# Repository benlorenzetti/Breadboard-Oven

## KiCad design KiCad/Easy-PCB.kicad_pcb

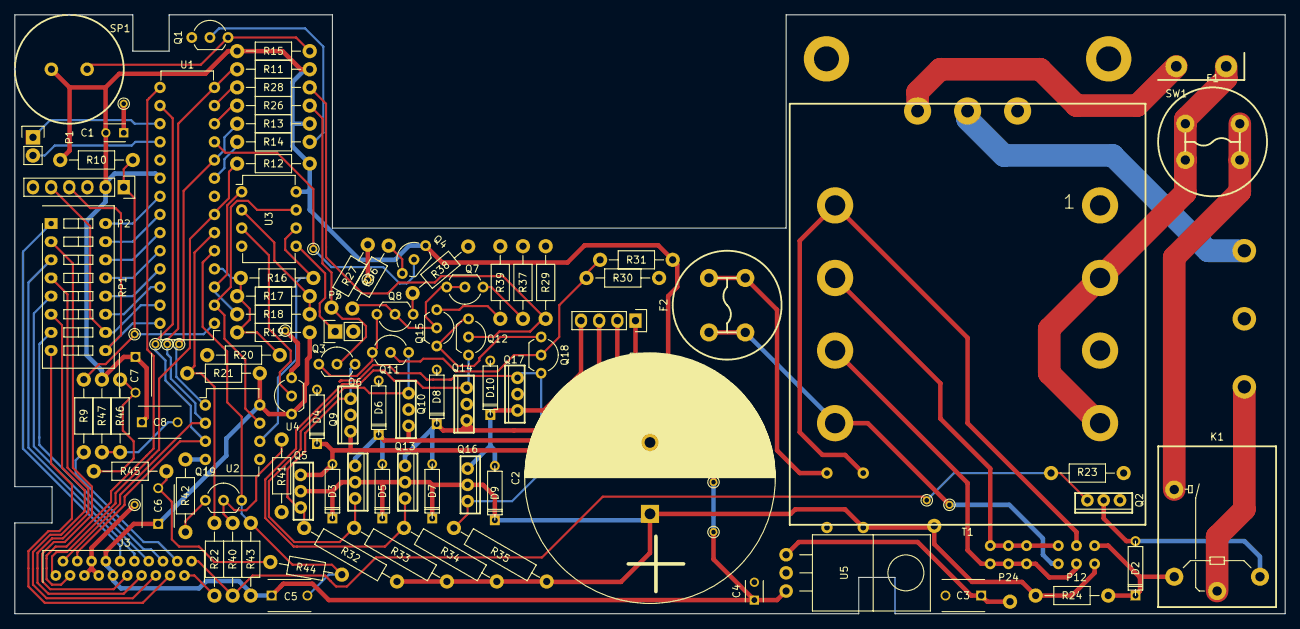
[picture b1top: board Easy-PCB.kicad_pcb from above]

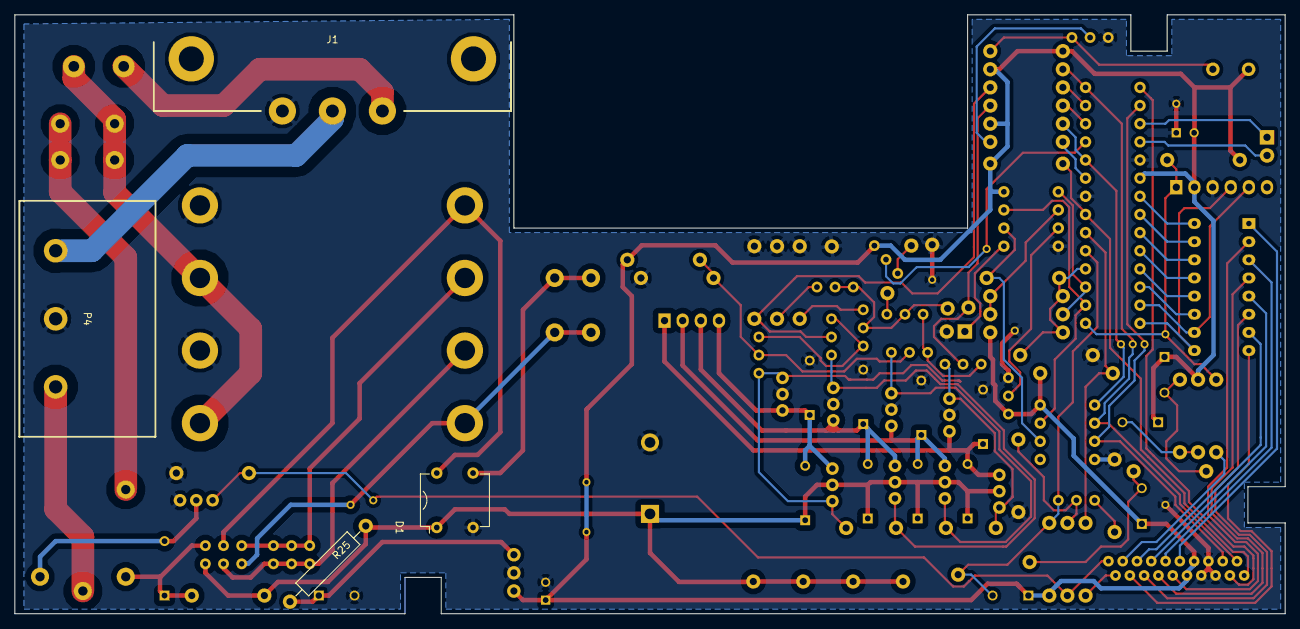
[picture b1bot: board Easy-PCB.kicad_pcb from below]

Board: 2 copper layers, 177.8 x 83.8 mm, 111 parts (4 on the bottom side), 81 nets.

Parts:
C1: 0.1u; C_Disc_D3_P2.5
C2: >16.6 mF; C_Radial_D35_L51_P10
C3: 0.33 uF; C_Disc_D6_P5
C4: 0.1 uF; C_Disc_D3_P2.5
C5, C6, C7, C8: CP1; C_Disc_D6_P5
D1: DF04M
D2: V*A(max) > 0.4 W; D3
D3, D4, D5, D6, D7, D8, D9, D10: D; D3
F1, F2: 83100000005; 83100000005_Fuse_Holder
J1: 703W-00/53; 703W-0053
J3: HLW20R-2C7LF
K1: G5LE-1A-E_DC12
P1, P5: 1x02; Socket_Strip_Straight_1x02
P2: 1x06; Socket_Strip_Straight_1x06
P3: 1x04; Socket_Strip_Straight_1x04
P4: 1x03 Terminal Block; 5-1437652-4
P6, P7, P8, P9, P10, P11, P13, P14, P15, P16, P17, P18, P19: via; PINTST
P12, P24: M20-9980346; Male_Header_2x03
P22: Screw Mounting; 10-32
Q1, Q3, Q4, Q7, Q8, Q11, Q12, Q15, Q18, Q19: 2N3904; TO-92
Q2, Q5, Q9, Q13, Q16: MJE340; MJE3x0
Q6, Q10, Q14, Q17: MJE350; MJE3x0
R9, R14, R15, R17, R20, R22: 1k; Resistor_Horizontal_RM10mm
R10, R11, R12, R13, R21: 10k; Resistor_Horizontal_RM10mm
R16: 100; Resistor_Horizontal_RM10mm
R18: 1.7k; Resistor_Horizontal_RM10mm
R19: 6.1k; Resistor_Horizontal_RM10mm
R23: 333; Resistor_Horizontal_RM10mm
R24: 330; Resistor_Horizontal_RM10mm
R25: 10 Ohm; >= 2W; Resistor_Horizontal_RM15mm
R26, R28: 140; Resistor_Horizontal_RM10mm
R27, R29: 115; Resistor_Horizontal_RM10mm
R30, R31: 64; Resistor_Horizontal_RM10mm
R32, R33, R34, R35: 165; Resistor_Horizontal_RM15mm
R36: 51; Resistor_Horizontal_RM10mm
R37, R38, R39: 10; Resistor_Horizontal_RM10mm
R40, R41, R42, R43, R44, R45, R46, R47: R; Resistor_Horizontal_RM10mm
RP1: 320; SW_DIP_x8_Slide
SP1: 2kHz Piezo; PS1420
SW1: R1966ABLKBLKFR
T1: VPP24-830
U1: PIC16F883; DIP-28
U2: MCP41050; DIP-8
U3: MCP617; DIP-8
U4: MCP9700A; TO-92
U5: LM7805; TO-220

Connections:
12Vrelay1: D2.1, K1.2, P12.6, R24.2
12Vrelay2: D2.2, K1.5, Q2.2
12or24VAC1: F2.1, F2.2, P8.1, P12.1, T1.12
12or24VAC2: D1.4, P12.4, T1.7
12or24VAC3: P12.3, P24.1, P24.3, P24.5, T1.10
12or24VAC4: P12.2, P24.2, P24.4, P24.6, T1.9
12or24VAC5: D1.3, F2.3, F2.4
/Analog Math/NichromeTemp: C5.2, Q19.3, R43.2, R44.2, U1.5
/Heat Relay/DoorC1: J3.19, R22.1
/Heat Relay/Heat: R21.2, R22.2, U1.6
/Heat Relay/HeatLive: K1.1, P4.1
/Motor Driver/wind1: R26.2, U1.12
/Motor Driver/wind1a: D3.2, D4.1, P3.1, Q5.1, Q6.1
/Motor Driver/wind1b: D5.2, D6.1, P3.2, Q9.1, Q10.1
/Motor Driver/wind2: R28.2, U1.13
/Motor Driver/wind2a: D7.2, D8.1, P3.3, Q13.1, Q14.1
/Motor Driver/wind2b: D9.2, D10.1, P3.4, Q16.1, Q17.1
/Power Circuit/MainsLive: F1.1, F1.2, SW1.2, T1.3, T1.6
/Temperature Feedback/K+: P5.1, U3.5
/Temperature Feedback/Tk: U1.2, U2.7, U3.7
/Temperature Feedback/Tref: R18.2, U1.3, U3.1
/Temperature Feedback/Vref-: R16.1, R17.1, R19.2, R20.1, U1.4
CS1: J3.1, R12.2, U1.7
CS2: P13.1, R13.2, U1.10, U2.1
DoorC2: J3.20, P9.1, Q2.3, R23.1, R40.2
Earth: J1.2, P4.3
GND: C1.1, C2.2, C3.2, C4.2, D1.2, D4.2, D6.2, D8.2, D10.2, J1.3, J3.5, J3.6, J3.7, P2.3, P4.2, P5.2, P14.1, P15.1, P17.1, P18.1, Q1.1, Q2.1, Q6.2, Q10.2, Q14.2, Q17.2, R20.2, R23.2, R27.2, R29.1, R31.2, R37.2, R38.2, R39.2, R41.2, R42.2, T1.1, T1.4, U1.8, U1.19, U2.4, U3.4, U4.3, U5.2
MISO: J3.3, U1.15
MOSI: J3.4, P10.1, U1.16, U2.3
Motor_On: P16.1, Q4.2, U1.11
unnamed: C6.2, R44.1, R45.2
unnamed: C7.2, R45.1, R46.2
unnamed: C8.2, R46.1, R47.2
unnamed: J1.1, SW1.1
unnamed: J3.10, RP1.1
unnamed: J3.11, RP1.2
unnamed: J3.12, RP1.3
unnamed: J3.13, RP1.4
unnamed: J3.14, RP1.5
unnamed: J3.15, RP1.6
unnamed: J3.16, RP1.7
unnamed: J3.17, RP1.8
unnamed: J3.18, R9.2
unnamed: P2.4, RP1.9, U1.28
unnamed: P2.5, RP1.10, U1.27
unnamed: Q1.2, R14.1
unnamed: Q1.3, R15.2, SP1.2
unnamed: Q3.2, R26.1, R27.1
unnamed: Q3.3, Q5.3, Q6.3, R32.2
unnamed: Q4.1, R36.2
unnamed: Q7.1, R37.1
unnamed: Q8.1, R38.1
unnamed: Q9.3, Q10.3, Q11.3, R33.2
unnamed: Q3.1, Q8.3, Q11.1
unnamed: Q11.2, Q18.2, R30.2, R31.1
unnamed: Q12.1, Q15.3, Q18.1
unnamed: Q12.2, R28.1, R29.2
unnamed: Q12.3, Q13.3, Q14.3, R34.2
unnamed: Q15.1, R39.1
unnamed: Q7.2, Q7.3, Q8.2, Q15.2, R36.1
unnamed: Q16.3, Q17.3, Q18.3, R35.2
unnamed: Q19.1, R42.1
unnamed: Q19.2, R40.1, R41.1
unnamed: R14.2, U1.9
unnamed: R16.2, U2.6, U3.6
unnamed: R17.2, R18.1, U3.2
unnamed: RP1.11, U1.26
unnamed: RP1.12, U1.25
unnamed: RP1.13, U1.24
unnamed: RP1.14, U1.23
unnamed: RP1.15, U1.22
unnamed: RP1.16, U1.21
unnamed: U3.3, U4.2
RX: P1.2, U1.18
Reset: P2.1, P19.1, R9.1, R10.2, U1.1
SCK: J3.2, P11.1, R11.2, U1.14, U2.2
TX: P1.1, U1.17
VAA: F1.3, F1.4, K1.3
VCC: C2.1, D1.1, D3.1, D5.1, D7.1, D9.1, P12.5, Q5.2, Q9.2, Q13.2, Q16.2, R24.1, R25.2, R32.1, R33.1, R34.1, R35.1
VDD: C1.2, C4.1, C5.1, C6.1, C7.1, C8.1, J3.8, J3.9, P2.2, P6.1, P7.1, Q4.3, R10.1, R11.1, R12.1, R13.1, R15.1, R19.1, R21.1, R30.1, R43.1, R47.1, SP1.1, U1.20, U2.8, U3.8, U4.1, U5.3
VDDunreg: C3.1, R25.1, U5.1

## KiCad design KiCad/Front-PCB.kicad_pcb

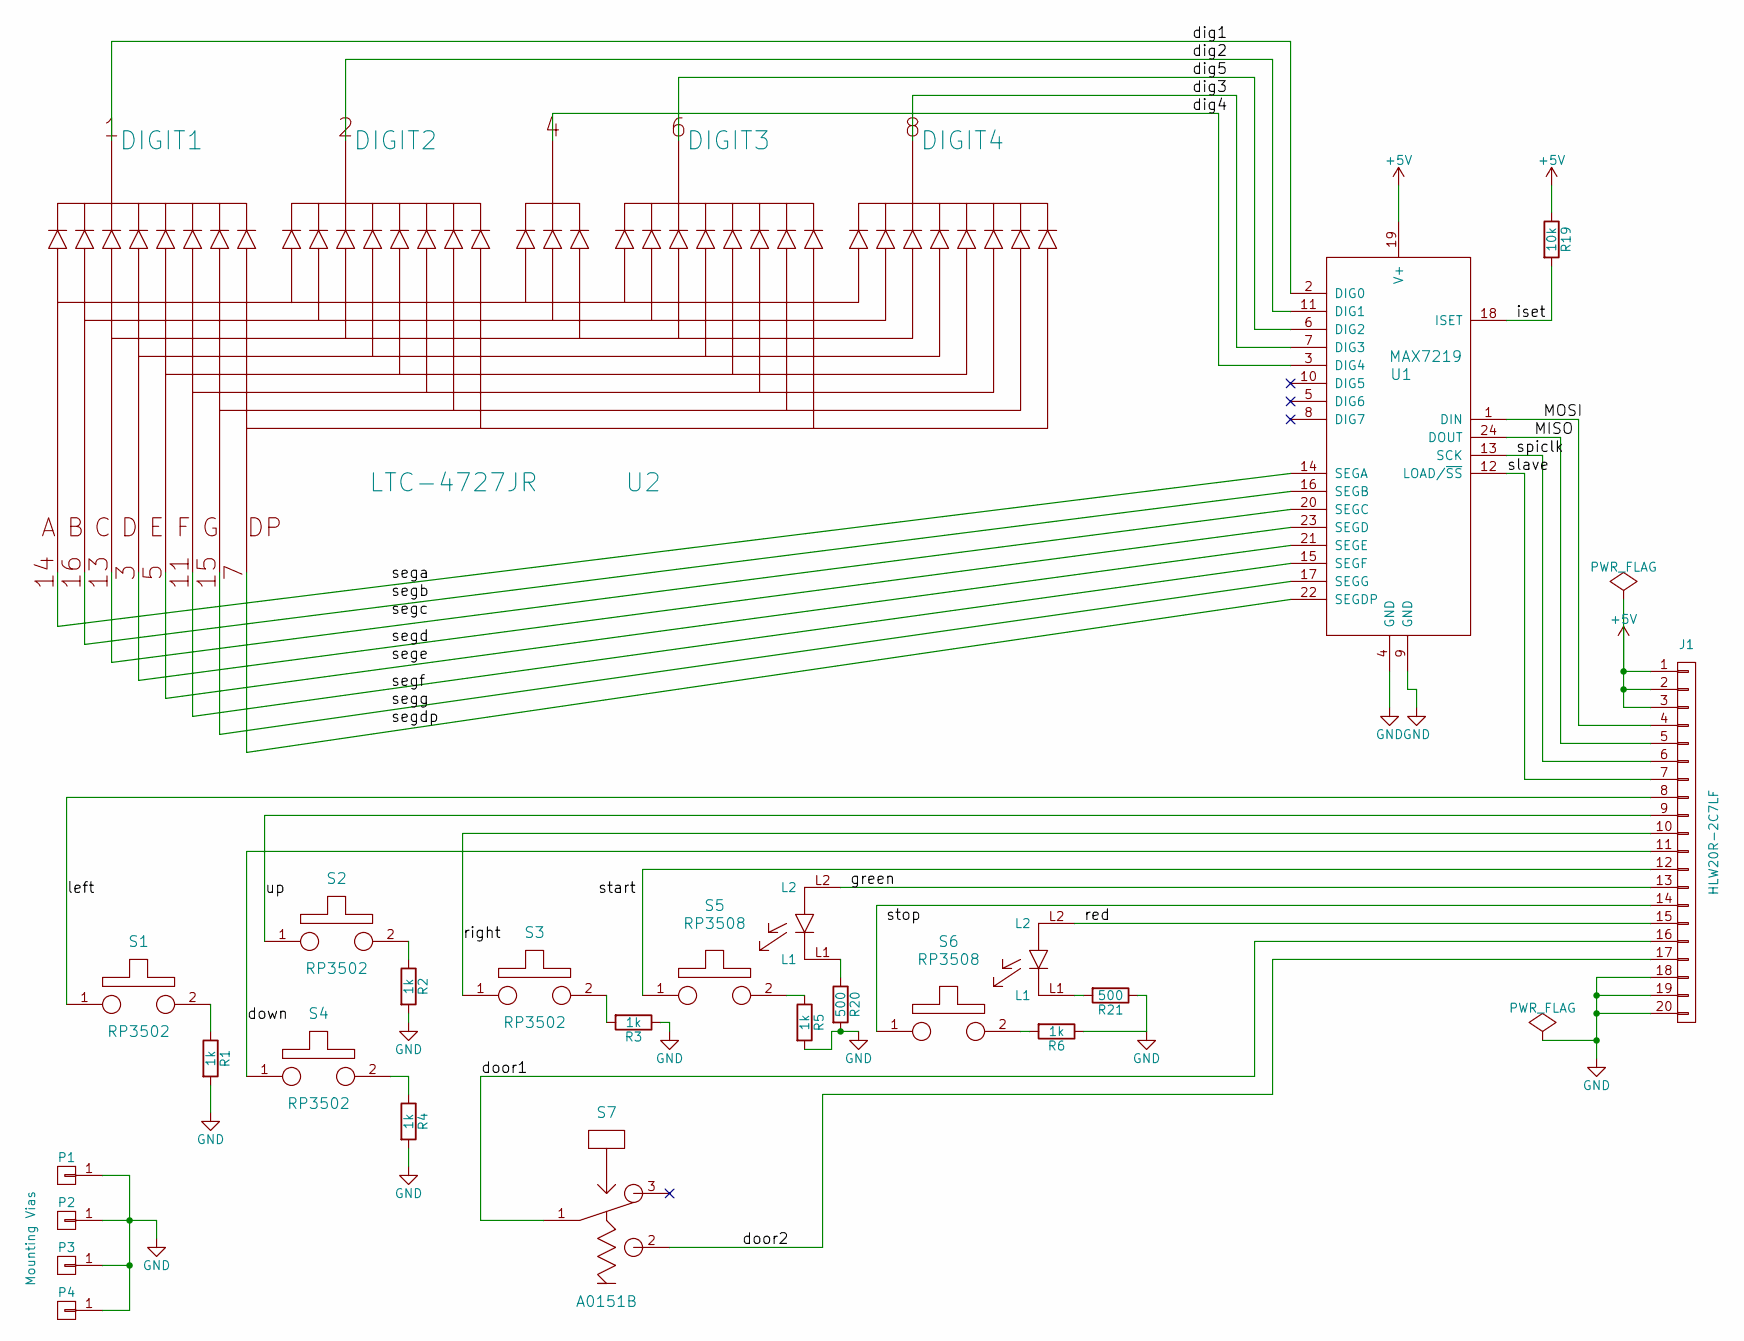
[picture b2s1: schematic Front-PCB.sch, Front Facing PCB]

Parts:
J1: HLW20R-2C7LF
P1: Mounting Vias; 10-32
P2, P3, P4: CONN_01X01; 10-32
R1, R2, R3, R4, R5, R6: 1k; R4
R19: 10k; R4
R20, R21: 500; R4
S1, S2, S3, S4: RP3502
S5, S6: RP3508
S7: A0151B
U1: MAX7219; 4824-3000-CP
U2: LTC-4727JR

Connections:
+5V: J1.1, J1.2, J1.3, R19.1, U1.19 (V+)
/MISO: J1.5, U1.24 (DOUT)
/MOSI: J1.4, U1.1 (DIN)
/dig1: U1.2 (DIG0), U2.1 (DIGIT1)
/dig2: U1.11 (DIG1), U2.2 (DIGIT2)
/dig3: U1.7 (DIG3), U2.8 (DIGIT4)
/dig4: U1.3 (DIG4), U2.4
/dig5: U1.6 (DIG2), U2.6 (DIGIT3)
/door1: J1.16, S7.1
/door2: J1.17, S7.2
/down: J1.11, S4.1
/green: J1.13, S5.L2
/iset: R19.2, U1.18 (ISET)
/left: J1.8, S1.1
/red: J1.15, S6.L2
/right: J1.10, S3.1
/slave: J1.7, U1.12 (LOAD/~SS)
/spiclk: J1.6, U1.13 (SCK)
/up: J1.9, S2.1
GND: J1.18, J1.19, J1.20, P1.1, P2.1, P3.1, P4.1, R1.2, R2.2, R3.1, R4.2, R5.2, R6.1, R20.2, R21.1, U1.4 (GND), U1.9 (GND)
unnamed: J1.12, S5.1
unnamed: J1.14, S6.1
unnamed: R1.1, S1.2
unnamed: R2.1, S2.2
unnamed: R3.2, S3.2
unnamed: R4.1, S4.2
unnamed: R5.1, S5.2
unnamed: R6.2, S6.2
unnamed: R20.1, S5.L1
unnamed: R21.2, S6.L1
unnamed: U1.14 (SEGA), U2.14
unnamed: U1.15 (SEGF), U2.11
unnamed: U1.16 (SEGB), U2.16
unnamed: U1.17 (SEGG), U2.15
unnamed: U1.20 (SEGC), U2.13
unnamed: U1.21 (SEGE), U2.5
unnamed: U1.22 (SEGDP), U2.7
unnamed: U1.23 (SEGD), U2.3

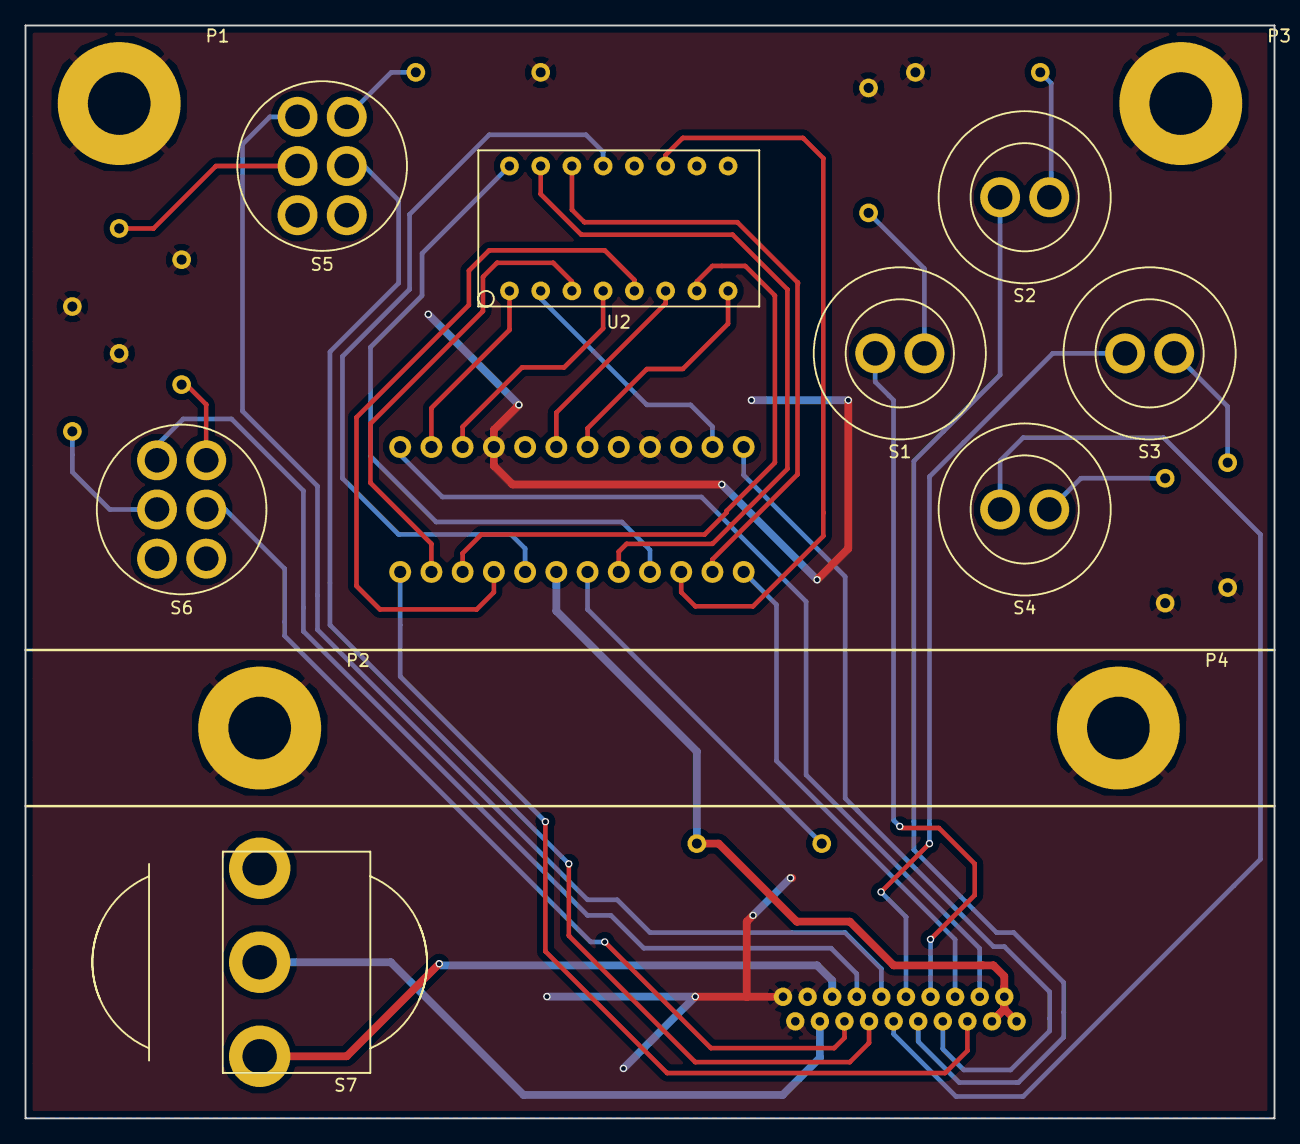
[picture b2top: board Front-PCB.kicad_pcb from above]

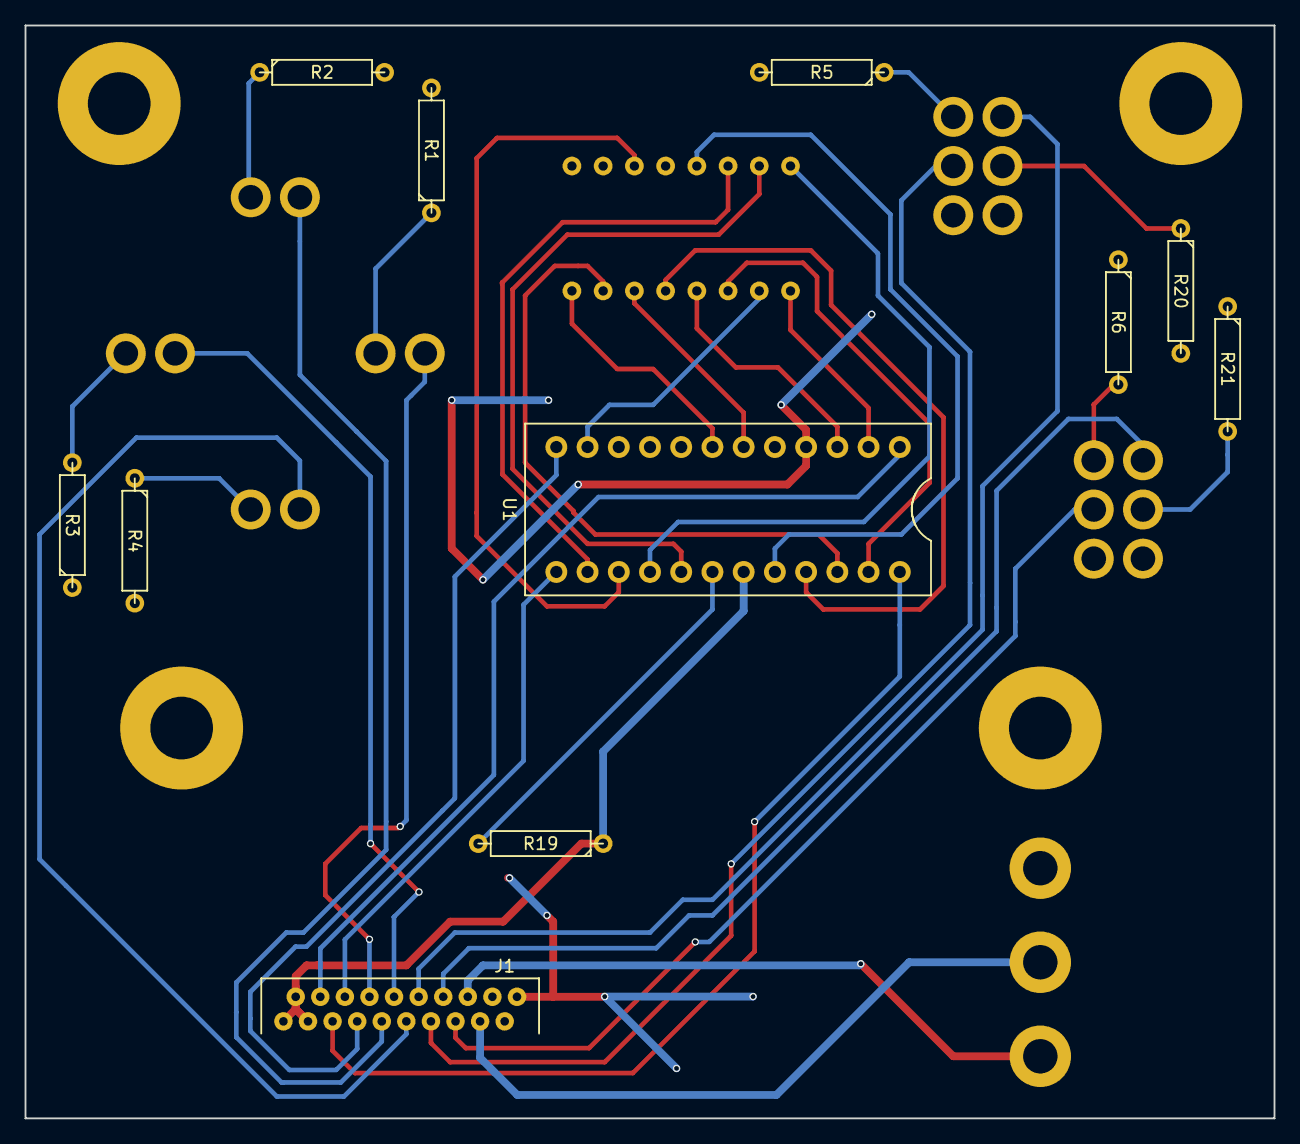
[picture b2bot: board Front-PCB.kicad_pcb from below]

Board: 2 copper layers, 101.6 x 88.9 mm, 23 parts (11 on the bottom side), 38 nets.

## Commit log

2015-10-08 testing .gitignore file for C code
2015-10-08 test gitignore again
2015-10-08 test gitignore 3
2015-10-08 test gitignore 4
2015-10-08 test gitignore 5
2015-10-08 test gitignore 6
2015-10-08 test gitignore 7
2015-10-08 test gitignore 8
2015-10-08 test gitignore 9
2015-10-08 test gitignore 10
2015-10-08 test gitignore 11
2015-10-08 test gitignore 12
2015-10-08 test gitignore 13
2015-10-08 Git Ignore Ok
2015-10-08 working on title
2015-10-09 title with photo
2015-10-15 files from PC recovery
2015-10-15 restored titlepage work
2015-10-15 features and introduction text
2015-10-15 Features/Introduction edits and formatting
2015-10-17 conceptual design-conduction through metals
2015-10-17 portion of newtons law proof
2015-11-07 AutoCAD iso generating script (only LINE is implemented)
2015-11-08 started bom with user interface components
2015-11-10 user interface text and temperature objectives
2015-11-11 LED display, std temp profile, and oven concept figures added
2015-11-13 user interface section complete
2015-11-13 heat conduction in 1d design equations
2015-11-13 editing
2015-11-13 thermodynamic theory section complete
2015-11-14 majority of newtons cooling law derivation
2015-11-14 cooling law heat transfer coefficients
2015-11-14 chamber air heat capacity
2015-11-14 edited text in chamber capacity and completed thermal properties table
2015-11-15 basic spice model complete
2015-11-17 simple nichrome wire model
2015-11-17 nichrome properties table and PCB trace width
2015-11-20 temperature feedback circuit
2015-11-21 aluminum components added to BOM and kicad library for 7-seg ICs
2015-11-21 Temperature feedback design
2015-11-21 user interface design section
2015-11-21 relays and flyback diodes
2015-11-22 thermodynamic model complete
2015-11-22 text edits
2015-11-22 motor driver section
2015-11-22 diagrams for heat circuit and control system added
2015-11-23 safety switch components added to bom and kicad lib
2015-11-23 front PCB schematic complete
2015-11-25 front panel erc
2015-11-25 kicad footprints and unrouted layout
2015-11-26 front panel pcb routing complete
2015-11-28 nichrome mounting parts added to bom and feedback terminal block removed
2015-11-28 motor driver edits
2015-11-28 Motor Driver BOM
2015-11-28 user interface updated with piezo alarm
2015-11-28 cleaned up git folder
2015-11-28 test new gitignore
2015-11-29 power circuit requirements section
2015-11-29 some of power circuit bom
2015-11-29 fixed nichrome wire resistance calculation and more power circuit bom
2015-11-30 several edits to report
2015-12-04 SPI functioning with display driver and 7-seg lookup table complete
2015-12-05 LED display function working and semi-merged with adams code
2015-12-05 before sending assembly to adam
2015-12-06 front PCB assembled and problems recorded in TODO
2015-12-06 interupt routing and timer0 outline complete
2015-12-07 Update_LED_Display() temperature portion complete
2015-12-07 piezo alarm implemented and new pushbuttons reconfigured
2015-12-08 display function debugged with multibyte times
2015-12-08 user interface working with 20 temp adding, 2 byte time, and compatibility function for indirect addressing
2015-12-09 thermocouple and runtime temperature/time display working
2015-12-09 three beep door open implemented
2015-12-11 lots added to report for embedded systems design report
2015-12-11 some text edits and controller and thermocouple circuit diagrams
2015-12-11 inputted most of BOM
2015-12-14 bom updates: relay resistors and motor connectors
2015-12-17 motor circuit working and switched to Fosc=8MHz...which is causing some pushbutton bugs
2015-12-17 motor variables speed macro and data memory organization macro
2015-12-18 edited introduction and started redo of motor driver design and 12 and 24 v rails
2015-12-22 updated circuit diagrams and started mechanical drawings
2015-12-24 adafruit and NMB motors front views
2015-12-26 updated temperature feedback schematic
2015-12-27 heat relay schematic and relay part updated-but not math in design section
2015-12-28 rather poorly written relay driver section
2015-12-28 microcontroller schematic kicad
2015-12-28 kicad motor and speaker schematics
2015-12-29 power circuit schematic in kicad
2015-12-29 controller board schematic complete
2015-12-29 HeatOn fix, replaced R1-8 with array
2015-12-31 motor driver design
2015-12-31 kicad resistor package associations complete
2016-01-01 capacitors and diode part associations
2016-01-02 temperature feedback resistor design
2016-01-02 IC BOM and footprints complete
2016-01-03 footprint associations complete
2016-01-03 errors cleared and components on board
2016-01-05 power port, switch, transformer, and relay in place
2016-01-05 power supply placed and routed
2016-01-06 power transistors mostly in place
2016-01-06 motor circuit routed
2016-01-07 reconfigured motor driver routing
2016-01-19 most of temperature feedback in place
2016-01-21 connector to front PCB routed
2016-01-23 routing complete
2016-01-24 added mounting cutouts to driver board
2016-02-01 new display driver, rot encoder, and stop button for front-facing pcb
2016-02-04 electronics BOM updated
2016-03-19 updated schematic pdfs
2017-08-23 synchronize PCs
